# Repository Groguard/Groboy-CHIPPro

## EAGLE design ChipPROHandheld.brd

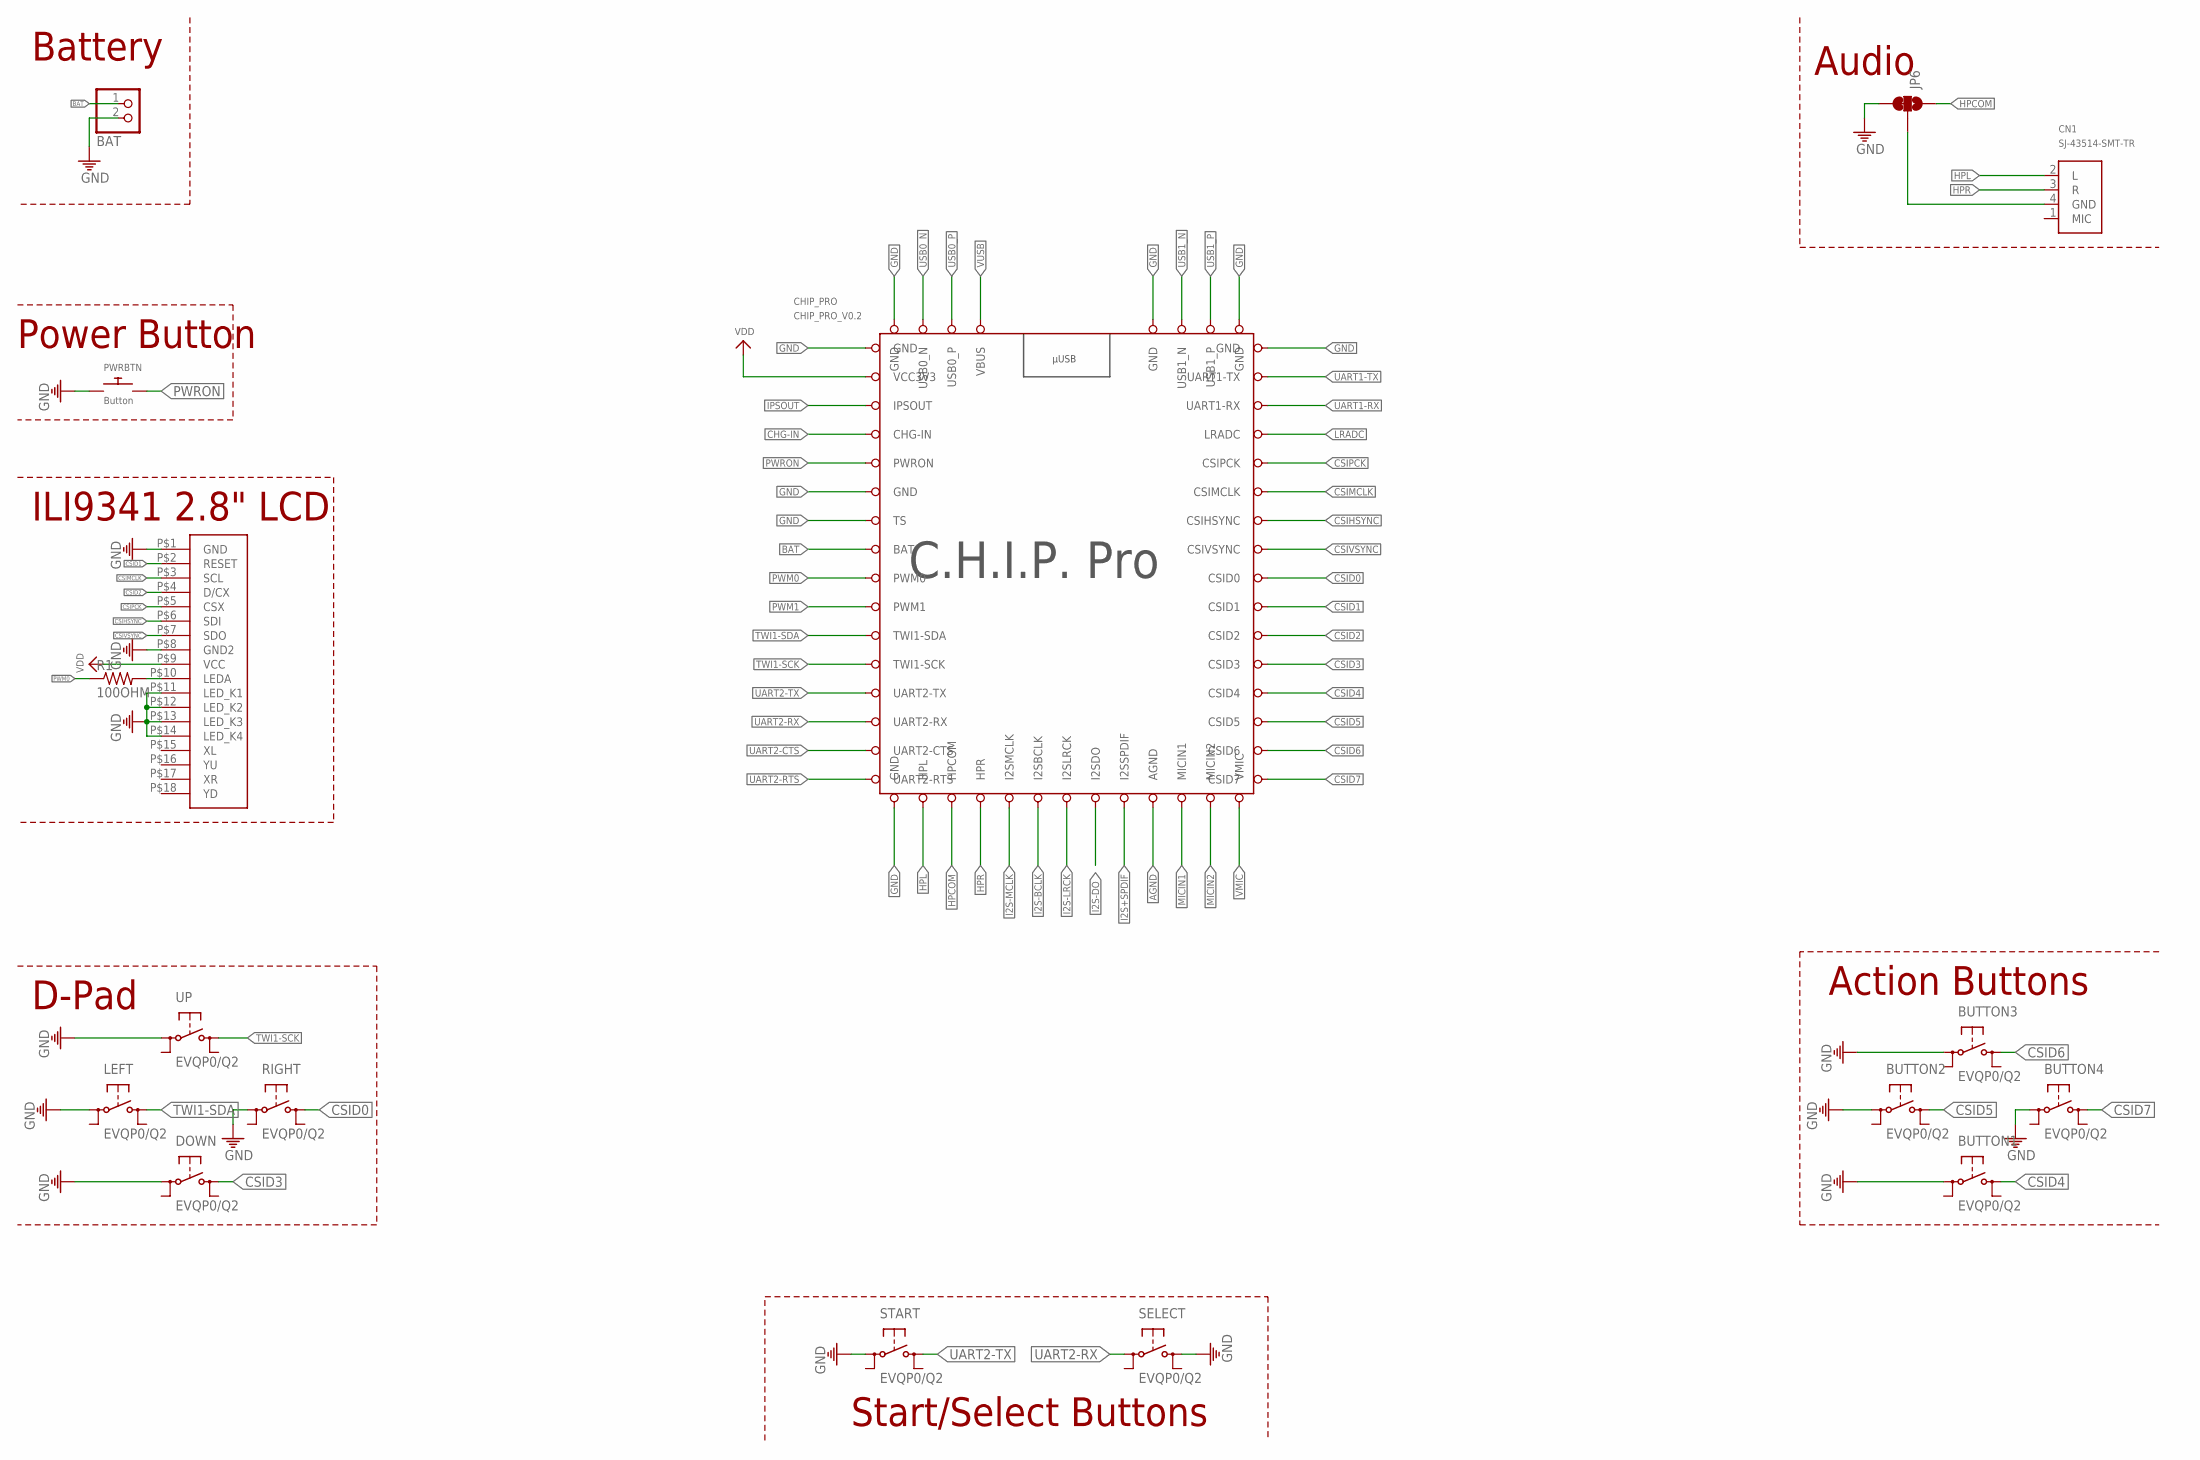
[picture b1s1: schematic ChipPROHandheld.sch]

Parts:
BAT: JST_2PIN-SMT-RA; JST-PH-2-SMT-RA
BUTTON1, BUTTON2, BUTTON3, BUTTON4: EVQP0/Q2
CHIP_PRO: CHIP_PRO_V0.2; GR8_MODULE_V0.2
CN1: SJ-43514-SMT-TR
DOWN: EVQP0/Q2
JP6: JUMPER-PAD-3-2OF3_NC_BY_TRACE_LARGE; PAD-JUMPER-3-2OF3_NC_BY_TRACE_YES_SILK_LARGE
LEFT: EVQP0/Q2
PWRBTN: Button; BTN_CK_KSS
R1: 100OHM; M0805
RIGHT: EVQP0/Q2
SELECT: EVQP0/Q2
START: EVQP0/Q2
U$7: ILI9341-2.2; ILI9341
UP: EVQP0/Q2

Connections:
AGND: CHIP_PRO.AGND
BAT: BAT.1 (2), CHIP_PRO.BAT
CHG-IN: CHIP_PRO.CHG-IN
CSID0: CHIP_PRO.CSID0, RIGHT.3 (S)
CSID1: CHIP_PRO.CSID1, U$7.P$2 (RESET)
CSID2: CHIP_PRO.CSID2, U$7.P$4 (D/CX)
CSID3: CHIP_PRO.CSID3, DOWN.3 (S)
CSID4: BUTTON1.3 (S), CHIP_PRO.CSID4
CSID5: BUTTON2.3 (S), CHIP_PRO.CSID5
CSID6: BUTTON3.3 (S), CHIP_PRO.CSID6
CSID7: BUTTON4.3 (S), CHIP_PRO.CSID7
CSIHSYNC: CHIP_PRO.CSIHSYNC, U$7.P$6 (SDI)
CSIMCLK: CHIP_PRO.CSIMCLK, U$7.P$3 (SCL)
CSIPCK: CHIP_PRO.CSIPCK, U$7.P$5 (CSX)
CSIVSYNC: CHIP_PRO.CSIVSYNC, U$7.P$7 (SDO)
GND: BAT.2 (1), BUTTON1.1, BUTTON2.1, BUTTON3.1, BUTTON4.1, CHIP_PRO.GND@0 (GND), CHIP_PRO.GND@1 (GND), CHIP_PRO.GND@2 (GND), CHIP_PRO.GND@3 (GND), CHIP_PRO.GND@4 (GND), CHIP_PRO.GND@6 (GND), CHIP_PRO.GND@7 (GND), CHIP_PRO.TS, DOWN.1, JP6.3, LEFT.1, PWRBTN.P$1, RIGHT.1, SELECT.3 (S), START.1, U$7.P$1 (GND), U$7.P$8 (GND2), U$7.P$11 (LED_K1), U$7.P$12 (LED_K2), U$7.P$13 (LED_K3), U$7.P$14 (LED_K4), UP.1
HPCOM: CHIP_PRO.HPCOM, JP6.1
HPL: CHIP_PRO.HPL, CN1.2 (L)
HPR: CHIP_PRO.HPR, CN1.3 (R)
I2S+SPDIF: CHIP_PRO.I2S+SPDIF (I2SSPDIF)
I2S-BCLK: CHIP_PRO.I2S-BCLK (I2SBCLK)
I2S-DO: CHIP_PRO.I2S-DO (I2SDO)
I2S-LRCK: CHIP_PRO.I2S-LRCK (I2SLRCK)
I2S-MCLK: CHIP_PRO.I2S-MCLK (I2SMCLK)
IPSOUT: CHIP_PRO.IPSOUT
LRADC: CHIP_PRO.LRADC
MICIN1: CHIP_PRO.MICIN1
MICIN2: CHIP_PRO.MICIN2
unnamed: R1.2, U$7.P$10 (LEDA)
unnamed: CN1.4 (GND), JP6.2
PWM0: CHIP_PRO.PWM0, R1.1
PWM1: CHIP_PRO.PWM1
PWRON: CHIP_PRO.PWRON, PWRBTN.P$2
TWI1-SCK: CHIP_PRO.TWI1-SCK, UP.3 (S)
TWI1-SDA: CHIP_PRO.TWI1-SDA, LEFT.3 (S)
UART1-RX: CHIP_PRO.UART1-RX
UART1-TX: CHIP_PRO.UART1-TX
UART2-CTS: CHIP_PRO.UART2-CTS
UART2-RTS: CHIP_PRO.UART2-RTS
UART2-RX: CHIP_PRO.UART2-RX, SELECT.1
UART2-TX: CHIP_PRO.UART2-TX, START.3 (S)
USB0_N: CHIP_PRO.USB0_N
USB0_P: CHIP_PRO.USB0_P
USB1_N: CHIP_PRO.USB1_N
USB1_P: CHIP_PRO.USB1_P
VDD: CHIP_PRO.VCC3V3, U$7.P$9 (VCC)
VMIC: CHIP_PRO.VMIC
VUSB: CHIP_PRO.VBUS

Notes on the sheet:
Audio
Action Buttons
D-Pad
Battery
Start/Select Buttons
Power Button
ILI9341 2.8" LCD

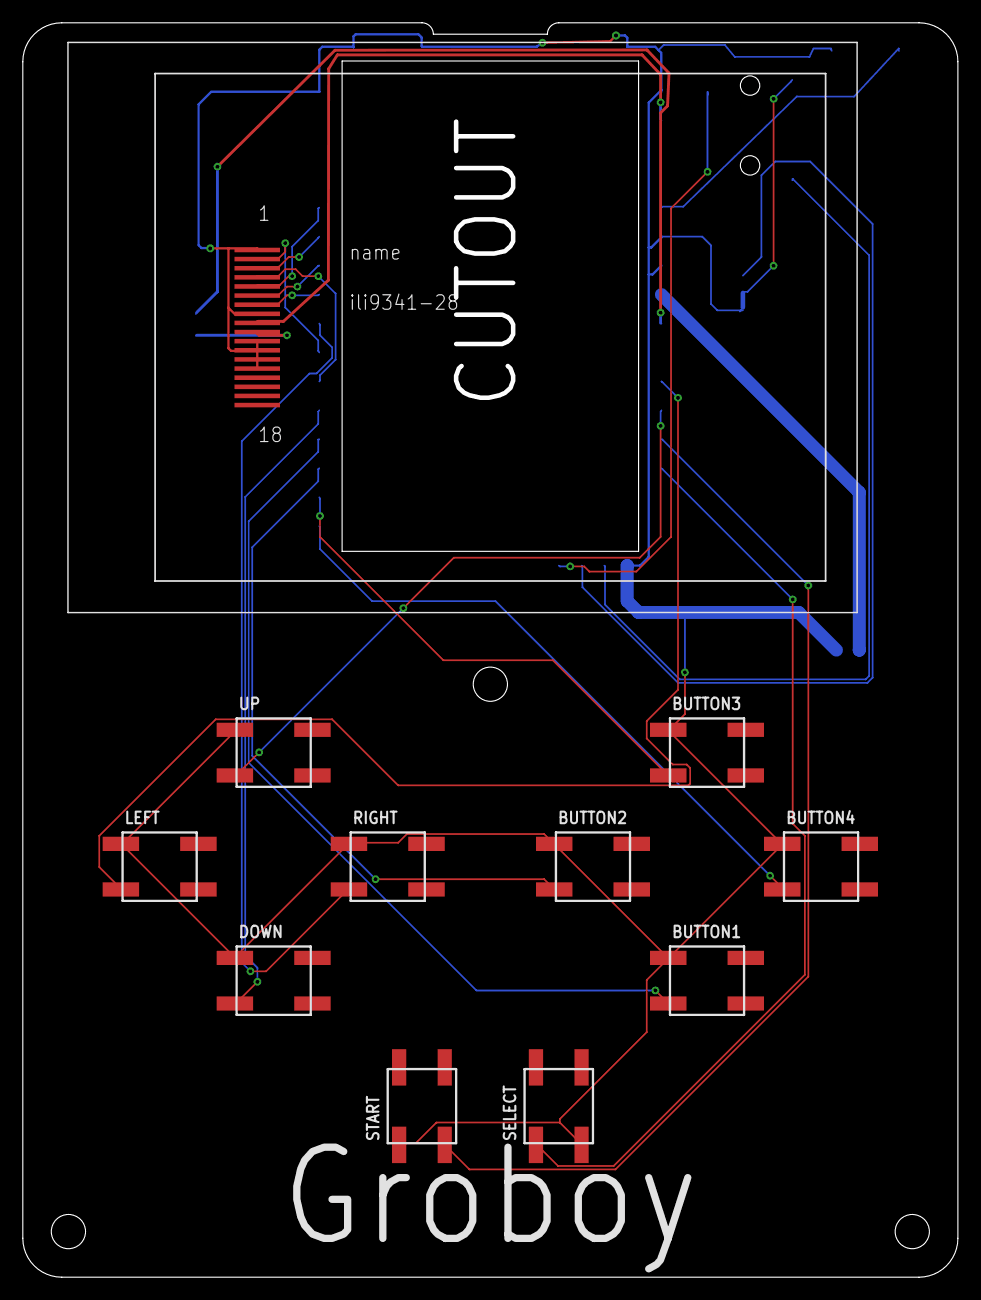
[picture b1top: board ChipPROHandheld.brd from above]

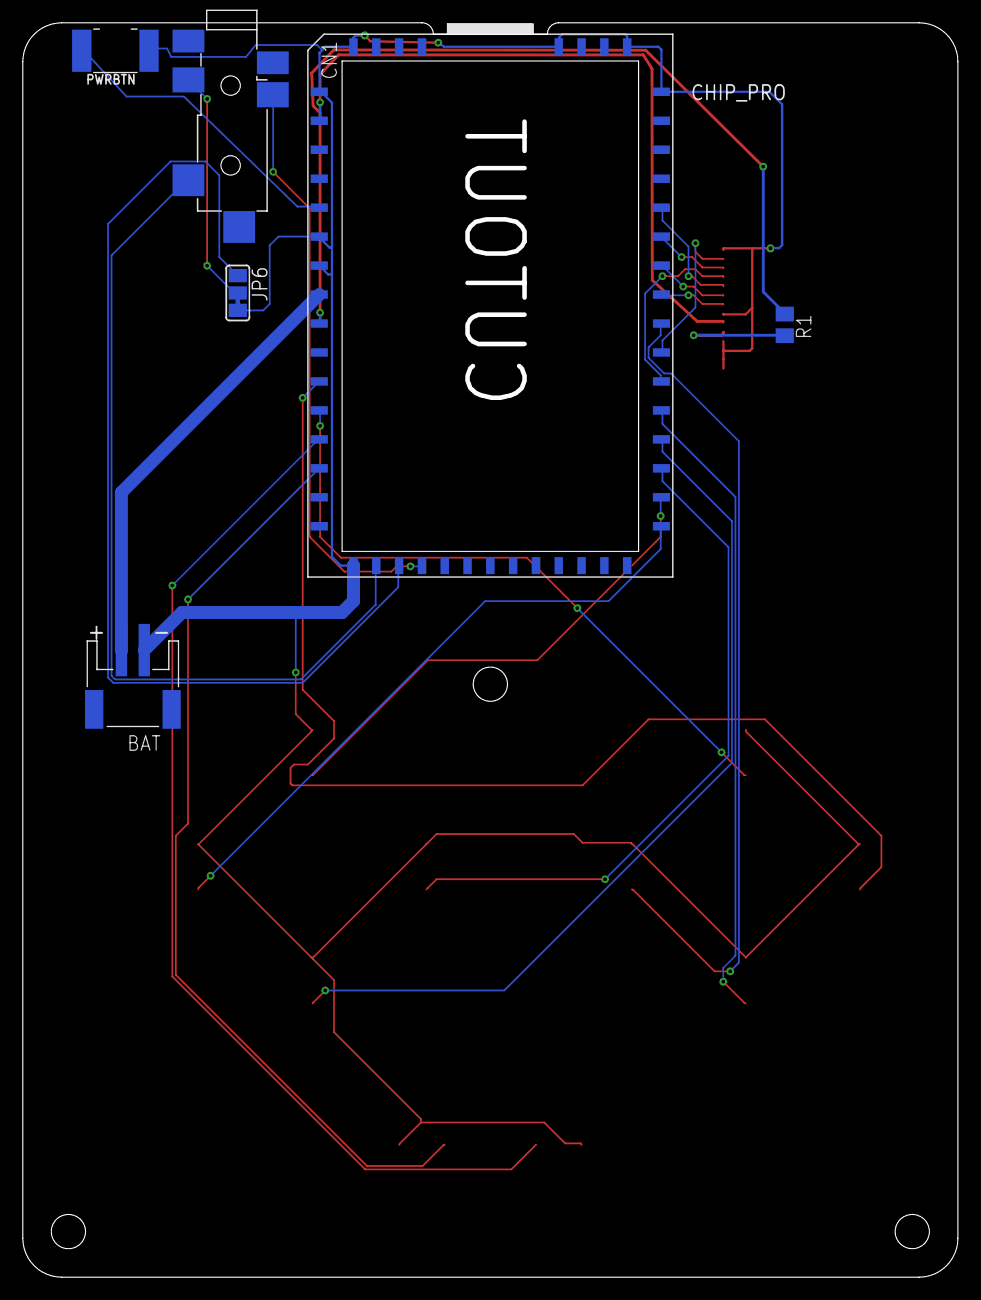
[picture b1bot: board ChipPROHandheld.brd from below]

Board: 2 copper layers, 82.0 x 110.0 mm, 17 parts (6 on the bottom side), 26 nets.

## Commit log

2020-07-23 First push
2020-07-23 remove empty files
2020-07-23 Reupload newer version

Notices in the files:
parts and their libraries:
switch-panasonic: Copyright (C) 2010, Bob Starr
SparkFun-Passives: Licensing: Creative Commons ShareAlike 4.0 International - https://creativecommons.org/licenses/by-sa/4.0
